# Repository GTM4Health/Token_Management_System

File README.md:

# GTM4Health — Token Management System

<p align="center">
  A real-time, web-based queue management system built for healthcare facilities.<br/>
  Patients receive numbered tokens, a main display shows who is being served, and staff control the queue from a dedicated calling unit.
</p>

---

## Table of Contents

1. [Overview](#overview)
2. [System Architecture](#system-architecture)
3. [Features](#features)
4. [Project Structure](#project-structure)
5. [Pages & Interfaces](#pages--interfaces)
6. [API Reference](#api-reference)
7. [Real-Time Events (Socket.IO)](#real-time-events-socketio)
8. [Database Schema](#database-schema)
9. [Setup & Installation](#setup--installation)
10. [Running Locally](#running-locally)
11. [Deployment](#deployment)
12. [ESP32 Hardware Integration](#esp32-hardware-integration)
13. [3D Design Files](#3d-design-files)

---

## Overview

The **GTM4Health Token Management System (TMS)** is a full-stack, real-time queue management solution designed to streamline patient flow in clinics and healthcare facilities. It eliminates manual queuing by issuing sequential numbered tokens and broadcasting live updates to all connected screens simultaneously via WebSockets.

**How it works end-to-end:**

```
Patient arrives → Gets a token from the Kiosk → Waits in lobby watching the Main Display
                                                         ↓
                                              Staff calls Next Token from Calling Unit
                                                         ↓
                                       Main Display updates live (with voice announcement)
                                                         ↓
                                              Patient proceeds to room
```

---

## System Architecture

```
┌─────────────────────────────────────────────────────────────────┐
│                        CLIENT LAYER                             │
│                                                                 │
│  ┌──────────────┐  ┌──────────────┐  ┌──────────────────────┐  │
│  │ Main Display │  │ Calling Unit │  │   Token Dispenser    │  │
│  │ (display.html│  │(operator.html│  │    (kiosk.html)      │  │
│  │   + TV/screen│  │   + tablet)  │  │ (tablet / ESP32)     │  │
│  └──────┬───────┘  └──────┬───────┘  └──────────┬───────────┘  │
│         │                 │                      │              │
└─────────┼─────────────────┼──────────────────────┼─────────────┘
          │  Socket.IO      │  REST API            │  REST API
          ▼                 ▼                      ▼
┌─────────────────────────────────────────────────────────────────┐
│                     SERVER LAYER (Flask)                        │
│               server.py  +  Flask-SocketIO  +  CORS            │
│                    Hosted on: Render.com                        │
└───────────────────────────────┬─────────────────────────────────┘
                                │
                                ▼
                    ┌───────────────────────┐
                    │   SQLite Database     │
                    │      token.db         │
                    │  (tokens table)       │
                    └───────────────────────┘
```

---

## Features

### Core Queue Management
- **Sequential Token Generation** — Tokens are issued as `001`, `002`, `003`, … (zero-padded, 3-digit format).
- **Call Next Token** — Operator calls the next waiting patient in FIFO order; the current token is automatically marked as `Completed`.
- **Call Again** — Re-broadcasts the currently serving token (useful if a patient didn't hear their number).
- **Call Specific Token** — Operator can skip to any token number by entering it manually.
- **Full Queue Reset** — Wipes all tokens and resets the counter back to `001`. Confirmation dialog prevents accidents.

### Real-Time Updates
- **Socket.IO WebSockets** — All screens (Main Display, Calling Unit, Kiosk) update instantly when the queue changes. No page refresh needed.
- **AJAX Polling Fallback** — Every 2 seconds, screens re-fetch the current token and waiting queue to stay in sync even if a Socket.IO event is missed.

### Main Display Extras
- **Text-to-Speech (TTS)** — When a token is called, the browser announces it aloud digit-by-digit (e.g., *"Token Zero, Zero, One. Please proceed to room."*) using the Web Speech API.
- **Live Waiting Queue** — A scrollable sidebar shows all tokens currently waiting, with a live count.
- **Reset Toast** — A non-intrusive notification banner appears when the queue is reset.
- **Responsive Design** — Works on full HD TVs, tablets, and mobile screens.

### Kiosk (Token Dispenser)
- Displays the latest generated token number prominently.
- Automatically opens a **print popup** (`/print/<token>`) when a new token is generated — ideal for thermal printers connected to the kiosk device.
- The print popup can be toggled on/off via `localStorage` (`printPopup` flag).
- Integrates with **ESP32** hardware for physical button-press token dispensing.

### Operator / Calling Unit
- Shows the **current serving token** prominently (190px font).
- **Manual Call** — Numeric input field to call any specific token by number.
- Buttons for: **Next**, **Call Again**, **Reset**.
- Live socket listener updates the displayed token automatically.

### Deployment & Integration
- Backend hosted on **Render.com** (Python web service).
- Frontend hosted on **Vercel** (`https://gtm-tms.vercel.app`).
- CORS and Socket.IO origins locked to the Vercel frontend for security.
- **Health check endpoint** at `/health` for uptime monitoring.

---

## Project Structure

```
Token_Management_System/
│
├── server.py                        # Flask backend — all API routes and Socket.IO events
├── requirements.txt                 # Python dependencies
├── token.db                         # SQLite database (auto-created on first run)
│
├── templates/
│   ├── display.html                 # Main Display — shown on TV/large screen in the lobby
│   ├── operator.html                # Calling Unit — used by clinic staff
│   ├── kiosk.html                   # Token Dispenser — patients generate their token here
│   └── print.html                   # Token Print Popup — thermal printer slip
│
├── static/
│   ├── logo.jpeg                    # GTM4Health organization logo
│   └── demologo.jpeg                # Demo/hospital partner logo (centered in header)
│
├── esp code/
│   └── finalintegrationw2devices/   # Arduino/ESP32 firmware for physical kiosk button
│
├── 3D design STL files for tms v1/  # STL files for Version 1 physical enclosure
├── 3D design STL files for tms v3/  # STL files for Version 3 physical enclosure
│
└── Documents and brochures/
    ├── TMS brochure v1.png
    ├── tech doc token management system.pdf
    └── tokenmanagementsystemreqdoc.pdf
```

---

## Pages & Interfaces

### 1. Main Display — `/` or `/display`

> **Intended for:** A large TV or monitor in the patient waiting area.

| Area | Description |
|------|-------------|
| **Left panel** | Shows the current token being served in large bold text (180px). Displays "Please proceed to the room" below it. |
| **Right panel** | Shows the live waiting queue — all tokens with `Waiting` status, with a count badge. |
| **Voice announcement** | When a token changes, the browser speaks it aloud using the Web Speech API. |
| **Apps menu** | Top-right hamburger menu (⊞) navigates between all three interfaces. |

---

### 2. Calling Unit (Operator Panel) — `/operator`

> **Intended for:** The clinic receptionist or staff member at the front desk.

| Control | Action |
|---------|--------|
| **Next Token** button | Marks current token as `Completed`, calls the next `Waiting` token as `Serving`. |
| **Call Again** button | Re-emits the `serving_changed` event for the currently serving token. |
| **Manual Token input + Call Token** | Enter any token number and call it directly, bypassing the queue order. |
| **Reset Queue** button | Deletes all tokens and resets the counter. Asks for confirmation first. |
| **Current Token display** | Shows the currently serving token in large text, auto-updates via Socket.IO. |

---

### 3. Token Dispenser (Kiosk) — `/kiosk`

> **Intended for:** A self-service tablet or ESP32-connected kiosk where patients arrive.

| Behaviour | Description |
|-----------|-------------|
| **Display on load** | Shows the most recently generated token in large text. |
| **On new token (Socket.IO)** | Updates displayed token and opens a print popup window (if enabled). |
| **Print popup** | Opens `/print/<token>` in a small popup — designed for thermal slip printing. |
| **Print toggle** | `localStorage.setItem("printPopup", "0")` disables the print popup. |

---

### 4. Print Slip — `/print/<token>`

> **Intended for:** Thermal printer connected to the kiosk.

A minimal, printable HTML page displaying the token number and branding. Automatically triggers `window.print()` on load.

---

## API Reference

All endpoints are served by the Flask backend at:  
`https://token-management-system-cvo8.onrender.com`

### GET Endpoints

| Endpoint | Description | Response |
|----------|-------------|----------|
| `GET /` | Renders Main Display page | HTML |
| `GET /display` | Alias for Main Display | HTML |
| `GET /operator` | Renders Calling Unit page | HTML |
| `GET /kiosk` | Renders Token Dispenser page | HTML |
| `GET /print/<token>` | Renders print slip for given token | HTML |
| `GET /current` | Returns the token currently being served | `{"token": "005"}` |
| `GET /latest` | Returns the last generated token number | `{"token": "007"}` |
| `GET /waiting` | Returns list of all waiting tokens (FIFO order) | `["003","004","005"]` |
| `GET /health` | Health check / uptime ping | `{"status": "online", "service": "..."}` |

### POST Endpoints

| Endpoint | Description | Request Body | Response |
|----------|-------------|--------------|----------|
| `POST /generate` | Generates the next sequential token and adds it to the queue with status `Waiting` | _(none)_ | `{"token": "008"}` |
| `POST /next` | Marks current `Serving` token as `Completed`, promotes oldest `Waiting` token to `Serving` | _(none)_ | `{"serving": "003"}` |
| `POST /call_again` | Re-emits the currently serving token to all clients | _(none)_ | `{"token": "003"}` |
| `POST /call_specific` | Calls a specific token number by jumping to it | `{"token": "005"}` | `{"message": "Called", "token": "005"}` |
| `POST /reset` | Deletes all tokens and resets the ID sequence | _(none)_ | `{"message": "Queue Reset Successfully", "token": "000"}` |

#### Error Responses

| Status | Meaning |
|--------|---------|
| `400` | Missing or invalid request body (e.g., token number not provided) |
| `404` | Token not found (used in `/call_specific`) |

---

## Real-Time Events (Socket.IO)

The server uses **Flask-SocketIO** with `eventlet` async mode. All clients connect to:  
`wss://token-management-system-cvo8.onrender.com`

### Events Emitted by Server → Clients

| Event | Payload | Triggered When |
|-------|---------|----------------|
| `new_token` | `{"token": "008"}` | A new token is generated via `POST /generate` |
| `serving_changed` | `{"token": "003"}` | A token is called via `/next`, `/call_again`, or `/call_specific` |
| `queue_reset` | _(no payload)_ | Queue is reset via `POST /reset` |

### How Each Page Responds

| Event | Main Display | Calling Unit | Kiosk |
|-------|-------------|-------------|-------|
| `new_token` | Refreshes waiting queue | _(not used)_ | Updates displayed token + opens print popup |
| `serving_changed` | Updates serving token, refreshes queue, triggers TTS | Updates current token display | _(not used)_ |
| `queue_reset` | Clears display, shows "---", shows toast | Clears current token | Resets to "000" |

---

## Database Schema

The system uses a single **SQLite** database (`token.db`) with one table:

```sql
CREATE TABLE IF NOT EXISTS tokens (
    id             INTEGER PRIMARY KEY AUTOINCREMENT,
    token          TEXT NOT NULL,          -- Zero-padded 3-digit number e.g. "007"
    status         TEXT NOT NULL,          -- "Waiting" | "Serving" | "Completed"
    generated_time TIMESTAMP DEFAULT CURRENT_TIMESTAMP
);
```

### Token Lifecycle

```
[Generated]  →  status = "Waiting"
     ↓
[Called]     →  status = "Serving"   (only one token can be Serving at a time)
     ↓
[Next called] → status = "Completed"
```

> **Note:** On queue reset, all rows are deleted and `sqlite_sequence` is cleared so token numbering restarts from `001`.

---

## Setup & Installation

### Prerequisites

- Python **3.9+**
- `pip` package manager
- A modern web browser (Chrome recommended for best TTS support)

### Step 1 — Clone the Repository

```bash
git clone https://github.com/your-org/Token_Management_System.git
cd Token_Management_System
```

### Step 2 — Create a Virtual Environment (Recommended)

```bash
# Windows
python -m venv venv
venv\Scripts\activate

# macOS / Linux
python3 -m venv venv
source venv/bin/activate
```

### Step 3 — Install Dependencies

```bash
pip install -r requirements.txt
```

**Dependencies installed:**

| Package | Purpose |
|---------|---------|
| `Flask` | Web framework and routing |
| `Flask-SocketIO` | WebSocket support via Socket.IO |
| `Flask-CORS` | Cross-Origin Resource Sharing headers |
| `eventlet` | Async networking for Socket.IO |

---

## Running Locally

### Start the Server

```bash
python server.py
```

The server starts on `http://0.0.0.0:5000` by default. Open your browser and navigate to:

| Interface | URL |
|-----------|-----|
| Main Display | http://localhost:5000/ |
| Calling Unit | http://localhost:5000/operator |
| Token Dispenser | http://localhost:5000/kiosk |
| Health Check | http://localhost:5000/health |

> **Note:** When running locally, the HTML templates hard-code the API URL to the **Render.com** hosted backend (`https://token-management-system-cvo8.onrender.com`). To test fully locally, update the `API_URL` constant in each HTML template from the Render URL to `http://localhost:5000`.

### Quick Local API Test (using curl or Postman)

```bash
# Generate a new token
curl -X POST http://localhost:5000/generate

# Get the current serving token
curl http://localhost:5000/current

# Get all waiting tokens
curl http://localhost:5000/waiting

# Call the next token
curl -X POST http://localhost:5000/next

# Call a specific token
curl -X POST http://localhost:5000/call_specific \
     -H "Content-Type: application/json" \
     -d '{"token": "003"}'

# Reset the queue
curl -X POST http://localhost:5000/reset
```

---

## Deployment

The project uses a **split deployment** architecture:

| Component | Platform | URL |
|-----------|----------|-----|
| Backend (Flask + Socket.IO) | [Render.com](https://render.com) | `https://token-management-system-cvo8.onrender.com` |
| Frontend (HTML served by Flask) | [Vercel](https://vercel.com) | `https://gtm-tms.vercel.app` |

### Deploying the Backend to Render

1. Push your repository to GitHub.
2. Create a new **Web Service** on Render.
3. Set the following:
   - **Build Command:** `pip install -r requirements.txt`
   - **Start Command:** `python server.py`
   - **Environment:** Python 3
4. Set the `PORT` environment variable if needed (Render auto-injects this).
5. CORS and Socket.IO origins in `server.py` are already scoped to `https://gtm-tms.vercel.app`.

### Environment Variables

| Variable | Default | Description |
|----------|---------|-------------|
| `PORT` | `5000` | Port the Flask server listens on. Render sets this automatically. |

> **Important:** The SQLite database (`token.db`) is stored on the server filesystem. On Render's free tier, the disk may reset on redeploy. For persistent storage across deployments, consider upgrading to a Render Disk or migrating to PostgreSQL.

---

## ESP32 Hardware Integration

The `esp code/finalintegrationw2devices/` folder contains **Arduino firmware** for a physical token dispensing kiosk built with an **ESP32** microcontroller.

### Hardware Overview

The ESP32 kiosk:
- Connects to Wi-Fi.
- Sends a `POST /generate` request to the backend when the patient presses a physical button.
- Can optionally drive a small thermal printer via serial to print the token slip.
- Works alongside the web-based kiosk interface (`kiosk.html`).

### Setup

1. Open the firmware in the Arduino IDE.
2. Update the Wi-Fi credentials (`ssid`, `password`) and the backend URL in the sketch.
3. Flash the firmware to your ESP32 board.
4. The device will connect to Wi-Fi and begin listening for button presses.

---

## 3D Design Files

Physical enclosure designs are provided as STL files for 3D printing:

| Folder | Version | Contents |
|--------|---------|---------|
| `3D design STL files for tms v1/` | v1 | First iteration of the physical kiosk enclosure |
| `3D design STL files for tms v3/` | v3 | Refined enclosure with improved fitment for ESP32 and printer |

STL files can be opened and sliced in tools like **Cura**, **PrusaSlicer**, or **Bambu Studio**.

---

## Project Roles

| Interface | User / Actor | Device |
|-----------|-------------|--------|
| **Main Display** | Patients in waiting area | TV / Large Monitor |
| **Token Dispenser (Kiosk)** | Arriving patients | Tablet / ESP32 kiosk |
| **Calling Unit (Operator)** | Clinic staff / receptionist | Tablet / Desktop |

---

## License

This project was developed by **GTM4Health**. All rights reserved.

---

<p align="center">© GTM4Health 2026</p>

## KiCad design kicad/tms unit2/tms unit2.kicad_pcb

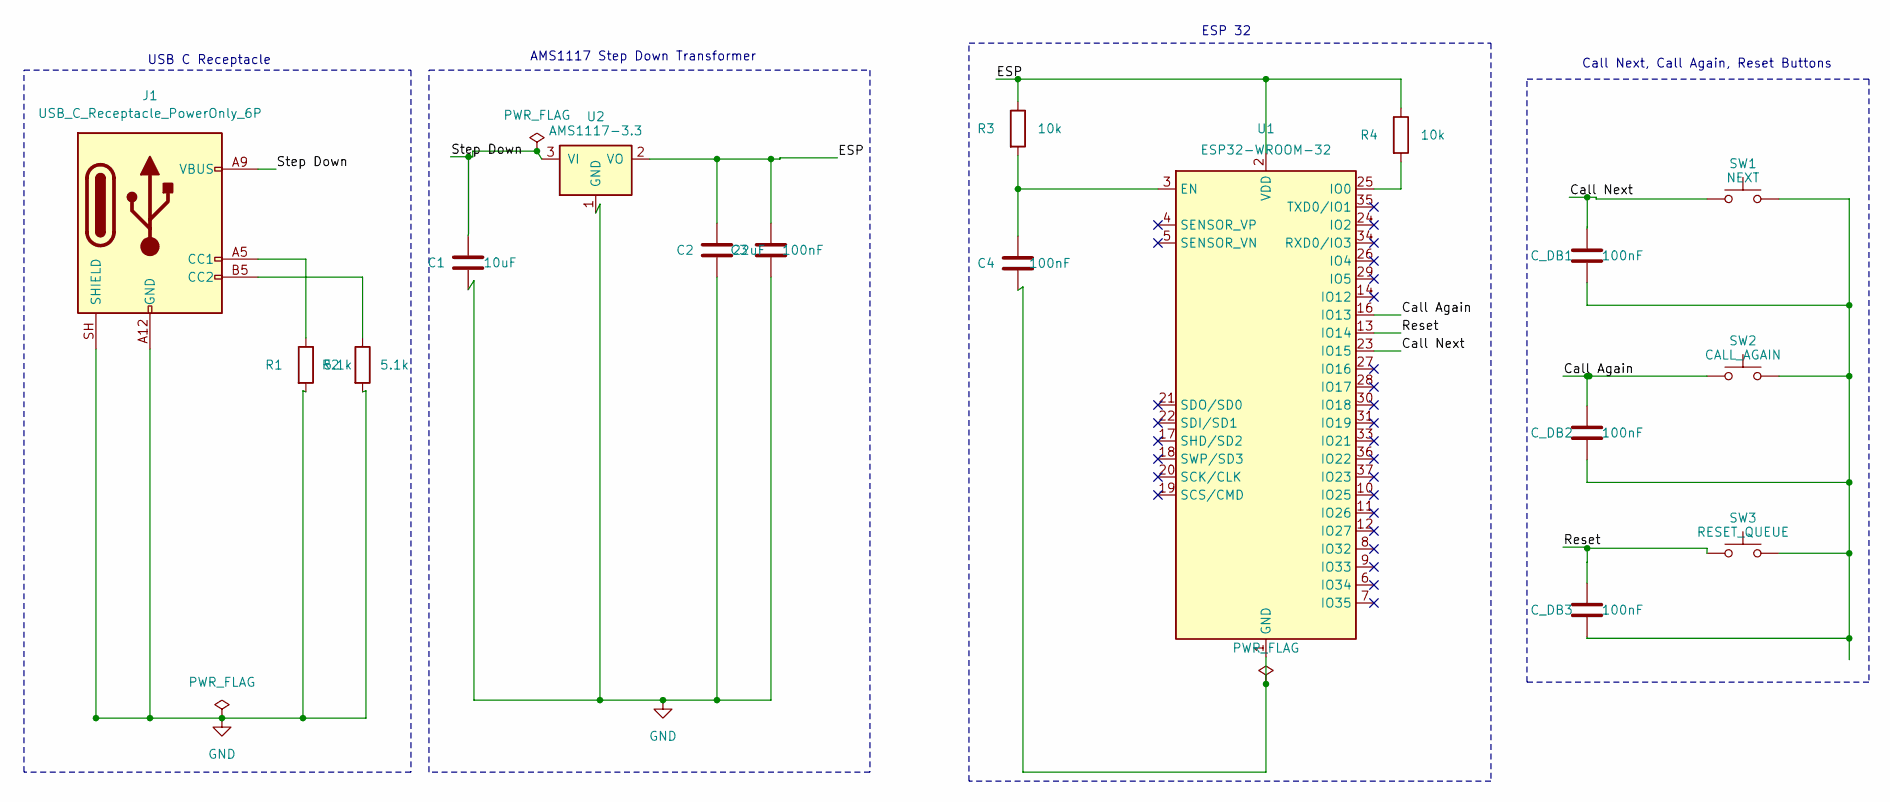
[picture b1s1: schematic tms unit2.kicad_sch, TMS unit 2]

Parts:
C1: 10uF; C_0805_2012Metric
C2: 22uF; C_0805_2012Metric
C3, C4: 100nF; C_0805_2012Metric
C_DB1, C_DB2, C_DB3: 100nF; C_0805_2012Metric
J1: USB_C_Receptacle_PowerOnly_6P; USB_C_Receptacle_GCT_USB4125-xx-x_6P_TopMnt_Horizontal
R1, R2: 5.1k; R_0805_2012Metric
R3, R4: 10k; R_0805_2012Metric
SW1: NEXT; SW_SPST_PTS645Sx43SMTR92
SW2: CALL_AGAIN; SW_SPST_PTS645Sx43SMTR92
SW3: RESET_QUEUE; SW_SPST_PTS645Sx43SMTR92
U1: ESP32-WROOM-32
U2: AMS1117-3.3; SOT-223-3_TabPin2

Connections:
/Call Again: C_DB2.1, SW2.1, U1.16 (IO13)
/Call Next: C_DB1.1, SW1.1, U1.23 (IO15)
/ESP: C2.1, C3.1, R3.1, R4.1, U1.2 (VDD), U2.2 (VO)
/Reset: C_DB3.1, SW3.1, U1.13 (IO14)
/Step Down: C1.1, J1.A9 (VBUS), J1.B9 (VBUS), U2.3 (VI)
GND: C1.2, C2.2, C3.2, J1.A12 (GND), J1.B12 (GND), J1.SH (SHIELD), R1.2, R2.2, U2.1 (GND)
unnamed: C4.2, U1.1 (GND), U1.15 (GND), U1.38 (GND), U1.39 (GND)
unnamed: C_DB1.2, C_DB2.2, C_DB3.2, SW1.2, SW2.2, SW3.2
unnamed: J1.A5 (CC1), R1.1
unnamed: J1.B5 (CC2), R2.1
unnamed: C4.1, R3.2, U1.3 (EN)
unnamed: R4.2, U1.25 (IO0)

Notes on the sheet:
Call Next, Call Again, Reset Buttons
AMS1117 Step Down Transformer
USB C Receptacle
ESP 32

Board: 2 copper layers, 17 parts (0 on the bottom side), 12 nets, no tracks yet.
